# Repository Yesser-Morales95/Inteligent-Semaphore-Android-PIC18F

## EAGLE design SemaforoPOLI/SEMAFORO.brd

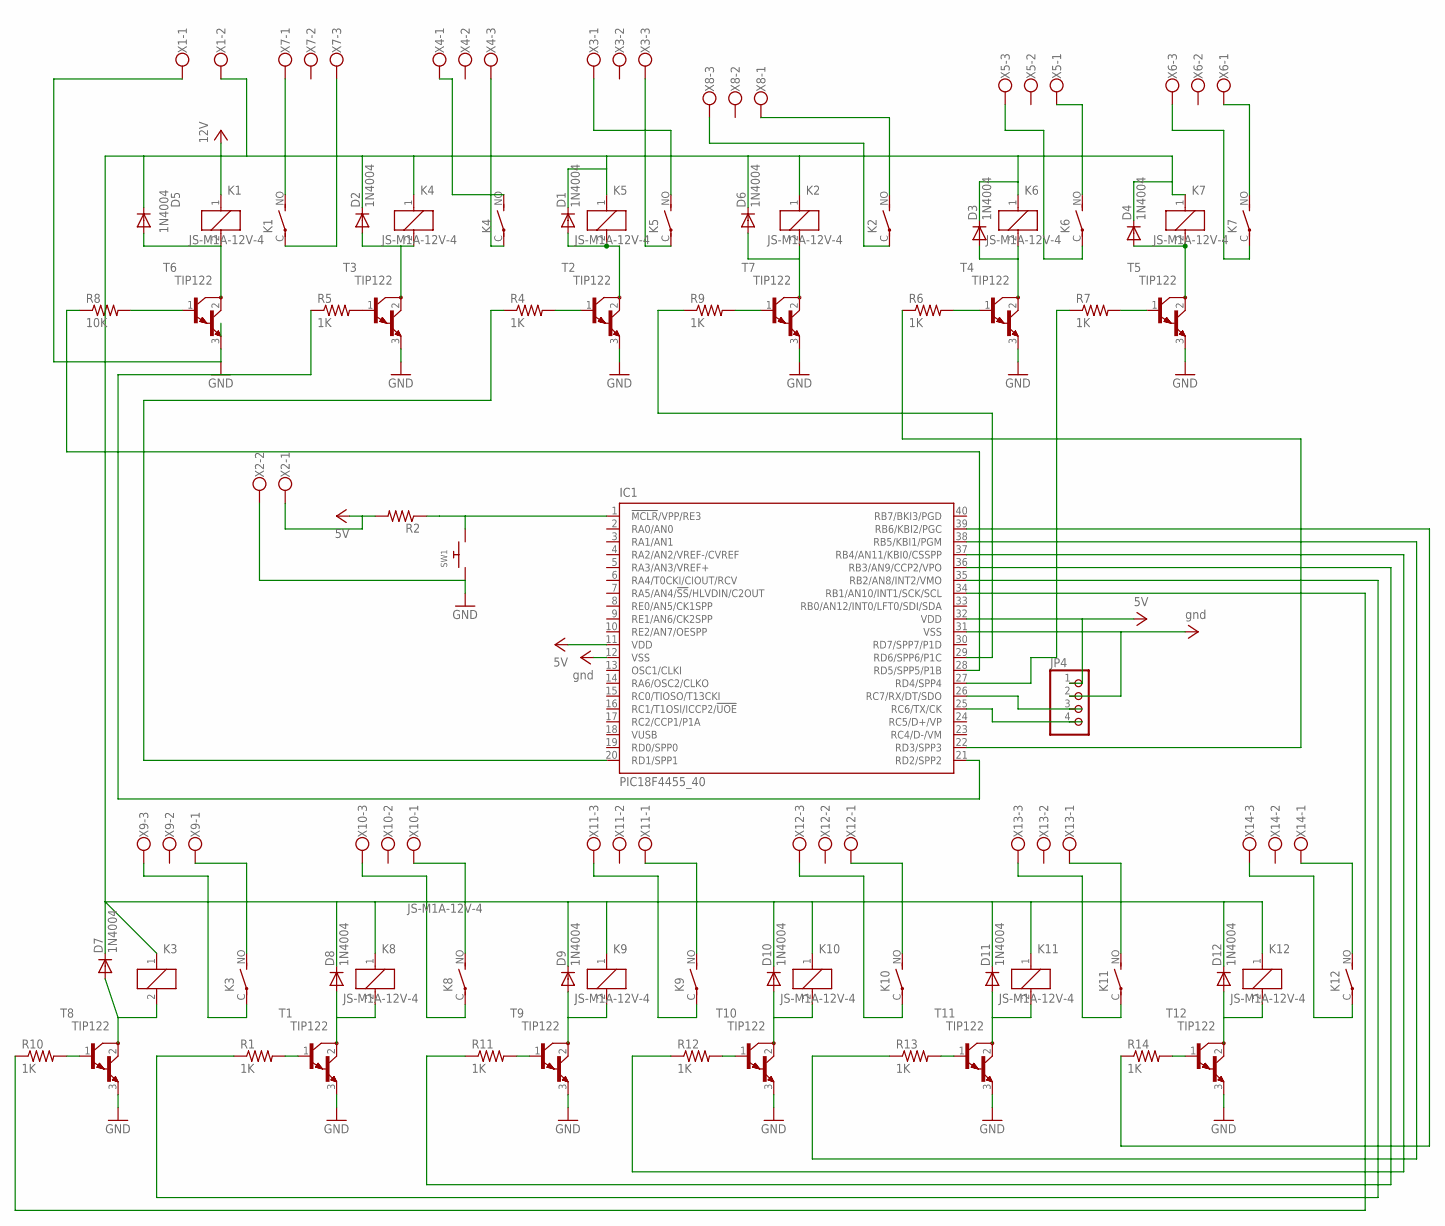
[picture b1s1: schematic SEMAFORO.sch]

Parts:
D1, D2, D3, D4, D5, D6, D7, D8, D9, D10, D11, D12: 1N4004; DO41-10
IC1: PIC18F4455_40; DIL40
JP4: PINHD-1X4; 1X04
K1, K2, K3, K4, K5, K6, K7, K8, K9, K10, K11, K12: JS-M1A-12V-4; JS-M1A
R1, R4, R5, R6, R7, R9, R10, R11, R12, R13, R14: 1K; 0207/10
R2: R-US_0207/10; 0207/10
R8: 10K; 0207/10
SW1: SWITCH_PUSHBUTTONEVQ-PE; TACT_PANA-EVQ
T1, T2, T3, T4, T5, T6, T7, T8, T9, T10, T11, T12: TIP122; TO220
X1, X2: W237-102
X3, X4, X5, X6, X7, X8, X9, X10, X11, X12, X13, X14: W237-103

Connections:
GND: IC1.12 (VSS), IC1.31 (VSS), JP4.2, SW1.P$1, T1.3 (E), T2.3 (E), T3.3 (E), T4.3 (E), T5.3 (E), T6.3 (E), T7.3 (E), T8.3 (E), T9.3 (E), T10.3 (E), T11.3 (E), T12.3 (E), X1.1, X2.2
unnamed: D8.A, K8.2, T1.2 (C)
unnamed: IC1.1 (!MCLR!/VPP/RE3), R2.1, SW1.P$2
unnamed: R8.2, T6.1 (B)
unnamed: D5.A, K1.2, T6.2 (C)
unnamed: K4.NO (S), X4.1
unnamed: K1.NO (S), X7.1
unnamed: R5.2, T3.1 (B)
unnamed: R1.2, T1.1 (B)
unnamed: IC1.21 (RD2/SPP2), R5.1
unnamed: K8.C, X10.3
unnamed: R4.2, T2.1 (B)
unnamed: D1.A, K5.2, T2.2 (C)
unnamed: K1.C, X7.3
unnamed: K8.NO (S), X10.1
unnamed: K6.NO (S), X5.1
unnamed: D2.A, K4.2, T3.2 (C)
unnamed: R9.2, T7.1 (B)
unnamed: D9.A, K9.2, T9.2 (C)
unnamed: R6.2, T4.1 (B)
unnamed: R11.2, T9.1 (B)
unnamed: R7.2, T5.1 (B)
unnamed: IC1.35 (RB2/AN8/INT2/VMO), R1.1
unnamed: IC1.20 (RD1/SPP1), R4.1
unnamed: D6.A, K2.2, T7.2 (C)
unnamed: K2.NO (S), X8.1
unnamed: K9.C, X11.3
unnamed: K2.C, X8.3
unnamed: D3.A, K6.2, T4.2 (C)
unnamed: K9.NO (S), X11.1
unnamed: D4.A, K7.2, T5.2 (C)
unnamed: D7.A, K3.2, T8.2 (C)
unnamed: R10.2, T8.1 (B)
unnamed: IC1.36 (RB3/AN9/CCP2/VPO), R11.1
unnamed: K3.C, X9.3
unnamed: K3.NO (S), X9.1
unnamed: IC1.37 (RB4/AN11/KBI0/CSSPP), R12.1
unnamed: IC1.25 (RC6/TX/CK), JP4.4
unnamed: IC1.26 (RC7/RX/DT/SDO), JP4.3
unnamed: D10.A, K10.2, T10.2 (C)
unnamed: K4.C, X4.3
unnamed: K5.NO (S), X3.1
unnamed: K5.C, X3.3
unnamed: K6.C, X5.3
unnamed: K7.NO (S), X6.1
unnamed: K7.C, X6.3
unnamed: R12.2, T10.1 (B)
unnamed: K10.C, X12.3
unnamed: K10.NO (S), X12.1
unnamed: D11.A, K11.2, T11.2 (C)
unnamed: R13.2, T11.1 (B)
unnamed: K11.C, X13.3
unnamed: K11.NO (S), X13.1
unnamed: D12.A, K12.2, T12.2 (C)
unnamed: R14.2, T12.1 (B)
unnamed: K12.C, X14.3
unnamed: K12.NO (S), X14.1
unnamed: IC1.27 (RD4/SPP4), R7.1
unnamed: IC1.22 (RD3/SPP3), R6.1
unnamed: IC1.28 (RD5/SPP5/P1B), R8.1
unnamed: IC1.29 (RD6/SPP6/P1C), R9.1
unnamed: IC1.38 (RB5/KBI1/PGM), R13.1
unnamed: IC1.34 (RB1/AN10/INT1/SCK/SCL), R10.1
unnamed: IC1.39 (RB6/KBI2/PGC), R14.1
VCC: IC1.11 (VDD), IC1.32 (VDD), JP4.1, R2.2, X2.1
VCC12: D1.C, D2.C, D3.C, D4.C, D5.C, D6.C, D7.C, D8.C, D9.C, D10.C, D11.C, D12.C, K1.1, K2.1, K3.1, K4.1, K5.1, K6.1, K7.1, K8.1, K9.1, K10.1, K11.1, K12.1, X1.2

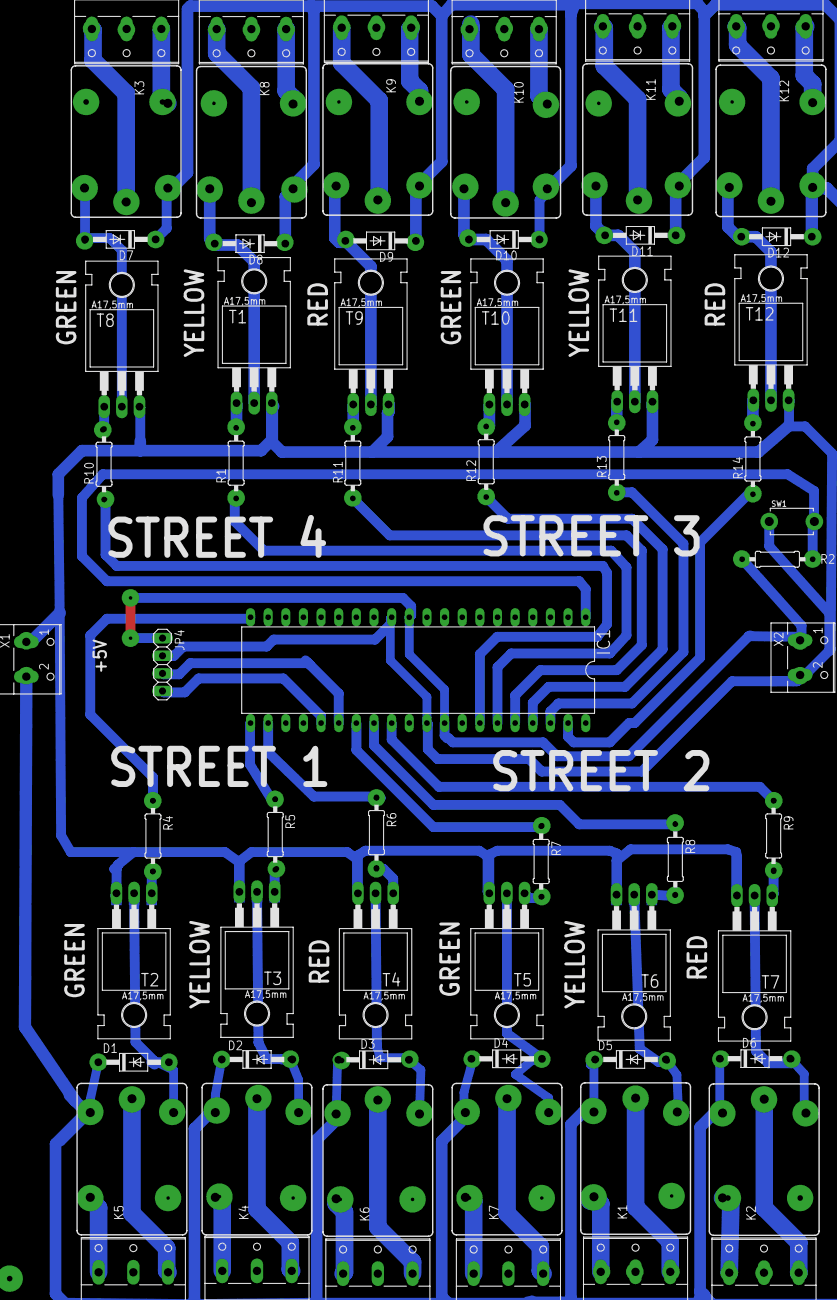
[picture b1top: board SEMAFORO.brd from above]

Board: 2 copper layers, 66 parts (0 on the bottom side), 66 nets.

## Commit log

2017-03-03 :neckbeard: Added .gitattributes & .gitignore files
2017-03-03 Project
    C, Android
